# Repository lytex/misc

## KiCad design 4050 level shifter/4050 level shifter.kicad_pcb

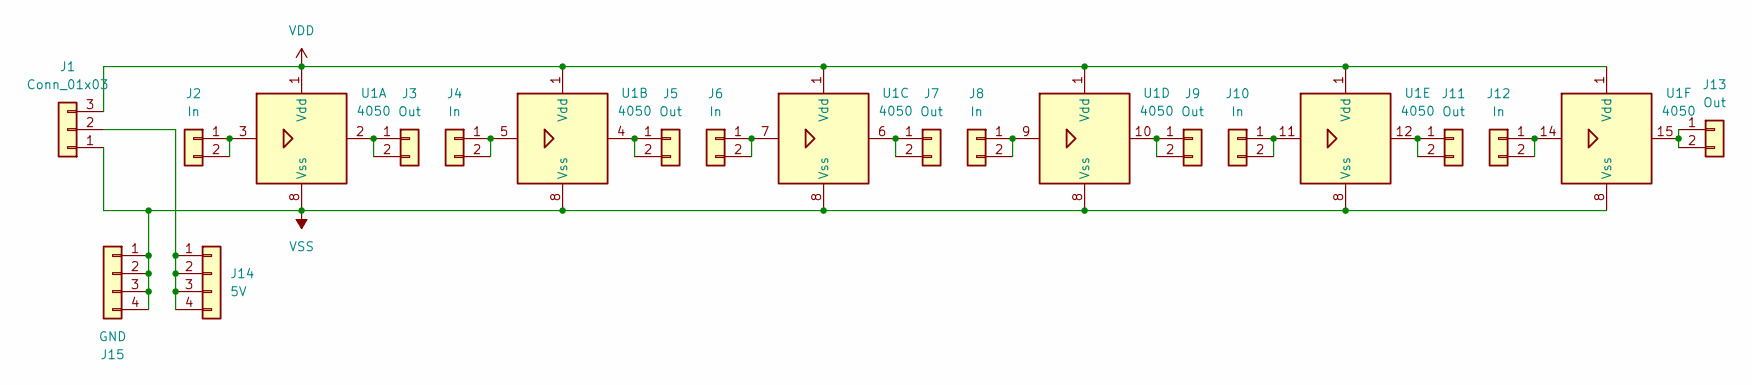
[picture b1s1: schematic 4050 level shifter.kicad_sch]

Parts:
J1: Conn_01x03; JST_EH_S3B-EH_1x03_P2.50mm_Horizontal
J2, J4, J6, J8, J10, J12: In; PinSocket_1x02_P2.54mm_Vertical
J3, J5, J7, J9, J11, J13: Out; PinSocket_1x02_P2.54mm_Vertical
J14: 5V; PinHeader_1x04_P2.54mm_Vertical
J15: GND; PinHeader_1x04_P2.54mm_Vertical
U1: 4050; DIP-16_W10.16mm

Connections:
unnamed: J1.2, J14.1, J14.2, J14.3, J14.4
unnamed: J2.1, J2.2, U1.3
unnamed: J3.1, J3.2, U1.2
unnamed: J4.1, J4.2, U1.5
unnamed: J5.1, J5.2, U1.4
unnamed: J6.1, J6.2, U1.7
unnamed: J7.1, J7.2, U1.6
unnamed: J8.1, J8.2, U1.9
unnamed: J9.1, J9.2, U1.10
unnamed: J10.1, J10.2, U1.11
unnamed: J11.1, J11.2, U1.12
unnamed: J12.1, J12.2, U1.14
unnamed: J13.1, J13.2, U1.15
VDD: J1.3, U1.1 (Vdd)
VSS: J1.1, J15.1, J15.2, J15.3, J15.4, U1.8 (Vss)

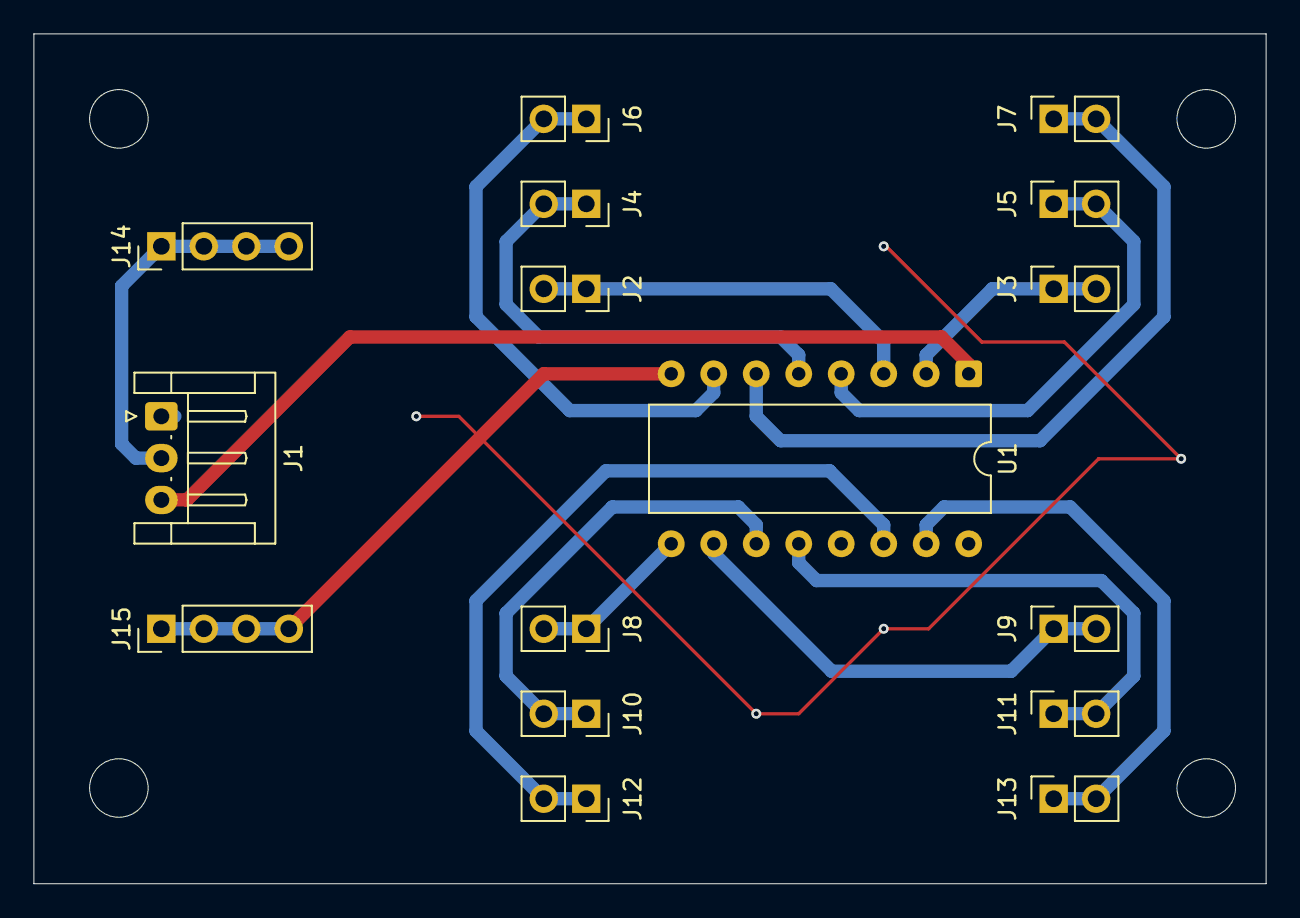
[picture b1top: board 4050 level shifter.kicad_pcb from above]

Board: 2 copper layers, 73.7 x 50.8 mm, 16 parts (0 on the bottom side), 15 nets.

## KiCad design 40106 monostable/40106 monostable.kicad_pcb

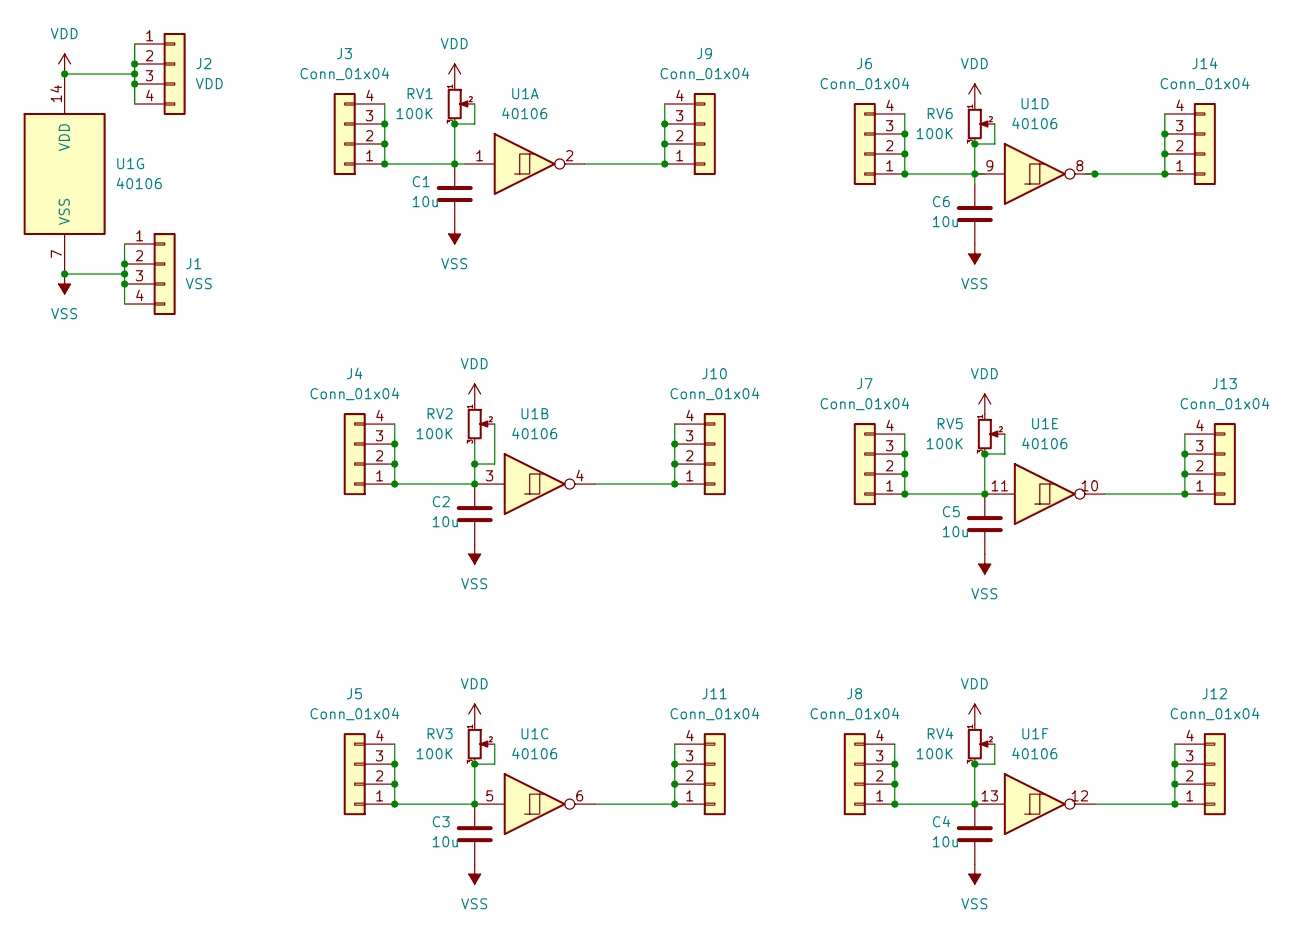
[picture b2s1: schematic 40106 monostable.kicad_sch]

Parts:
C1, C2, C3, C4, C5, C6: 10u; C_Disc_D7.5mm_W2.5mm_P5.00mm
J1: VSS; PinHeader_1x04_P2.54mm_Vertical
J2: VDD; PinHeader_1x04_P2.54mm_Vertical
J3, J4, J5, J6, J7, J8, J9, J10, J11, J12, J13, J14: Conn_01x04; PinHeader_1x04_P2.54mm_Vertical
RV1, RV2, RV3, RV4, RV5, RV6: 100K; Potentiometer_Alpha_RD901F-40-00D_Single_Vertical
U1: 40106; DIP-14_W10.16mm

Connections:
unnamed: C1.1, J3.1, J3.2, J3.3, J3.4, RV1.2, RV1.3, U1.1
unnamed: C2.1, J4.1, J4.2, J4.3, J4.4, RV2.2, RV2.3, U1.3
unnamed: C3.1, J5.1, J5.2, J5.3, J5.4, RV3.2, RV3.3, U1.5
unnamed: C6.1, J6.1, J6.2, J6.3, J6.4, RV6.2, RV6.3, U1.9
unnamed: C5.1, J7.1, J7.2, J7.3, J7.4, RV5.2, RV5.3, U1.11
unnamed: C4.1, J8.1, J8.2, J8.3, J8.4, RV4.2, RV4.3, U1.13
unnamed: J9.1, J9.2, J9.3, J9.4, U1.2
unnamed: J10.1, J10.2, J10.3, J10.4, U1.4
unnamed: J11.1, J11.2, J11.3, J11.4, U1.6
unnamed: J12.1, J12.2, J12.3, J12.4, U1.12
unnamed: J13.1, J13.2, J13.3, J13.4, U1.10
unnamed: J14.1, J14.2, J14.3, J14.4, U1.8
VDD: J2.1, J2.2, J2.3, J2.4, RV1.1, RV2.1, RV3.1, RV4.1, RV5.1, RV6.1, U1.14 (VDD)
VSS: C1.2, C2.2, C3.2, C4.2, C5.2, C6.2, J1.1, J1.2, J1.3, J1.4, U1.7 (VSS)

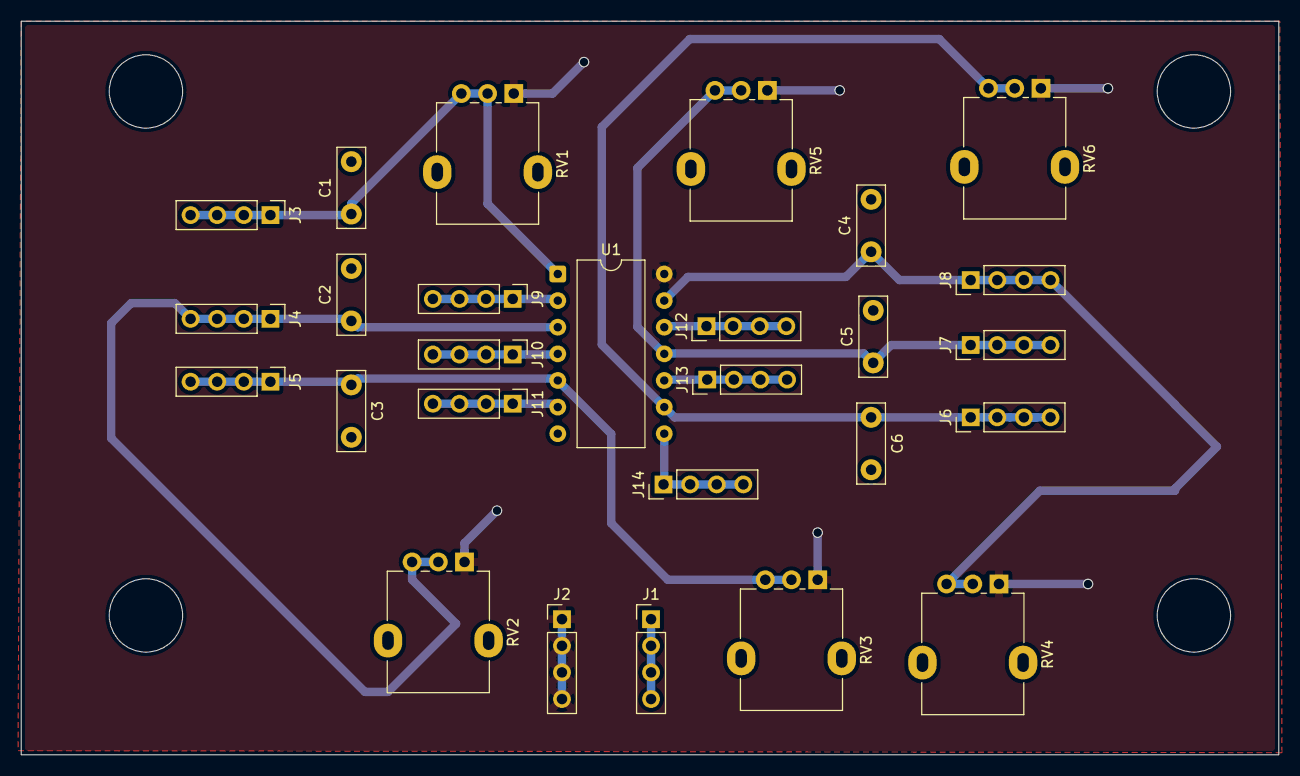
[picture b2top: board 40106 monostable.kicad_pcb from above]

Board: 2 copper layers, 120.0 x 70.0 mm, 27 parts (0 on the bottom side), 14 nets.

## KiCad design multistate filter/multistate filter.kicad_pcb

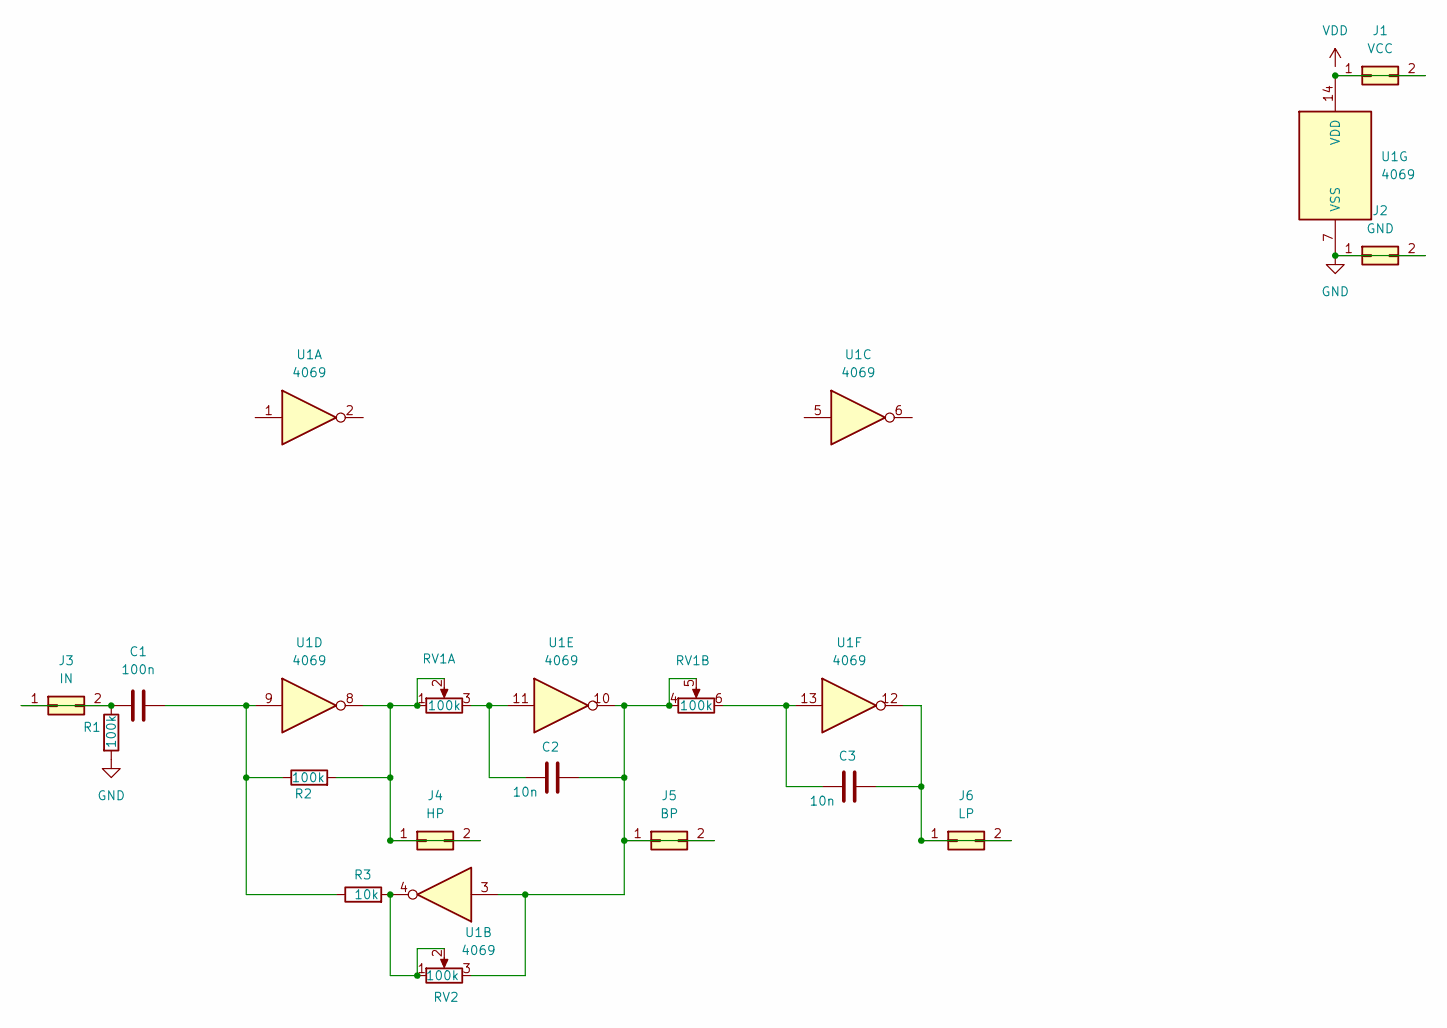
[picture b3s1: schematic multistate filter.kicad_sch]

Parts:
C1: 100n; C_Disc_D3.0mm_W1.6mm_P2.50mm
C2, C3: 10n; C_Disc_D3.0mm_W1.6mm_P2.50mm
J1: VCC; PinHeader_2x01_P2.54mm_Vertical
J2: GND; PinHeader_2x01_P2.54mm_Vertical
J3: IN; PinHeader_2x01_P2.54mm_Vertical
J4: HP; PinHeader_2x01_P2.54mm_Vertical
J5: BP; PinHeader_2x01_P2.54mm_Vertical
J6: LP; PinHeader_2x01_P2.54mm_Vertical
R1, R2: 100k; R_Axial_DIN0207_L6.3mm_D2.5mm_P10.16mm_Horizontal
R3: 10k; R_Axial_DIN0207_L6.3mm_D2.5mm_P10.16mm_Horizontal
RV1: 100k; Potentiometer_Alps_RK163_Dual_Horizontal
RV2: 100k; Potentiometer_Alps_RK163_Single_Horizontal
U1: 4069; DIP-14_W7.62mm

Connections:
GND: J2.1, J2.2, R1.2, U1.7 (VSS)
unnamed: C1.2, R2.1, R3.1, U1.9
unnamed: C2.1, RV1.3, U1.11
unnamed: C3.1, RV1.6, U1.13
unnamed: J1.1, J1.2, U1.14 (VDD)
unnamed: C1.1, J3.1, J3.2, R1.1
unnamed: J4.1, J4.2, R2.2, RV1.1, RV1.2, U1.8
unnamed: C2.2, J5.1, J5.2, RV1.4, RV1.5, RV2.3, U1.3, U1.10
unnamed: C3.2, J6.1, J6.2, U1.12
unnamed: R3.2, RV2.1, RV2.2, U1.4

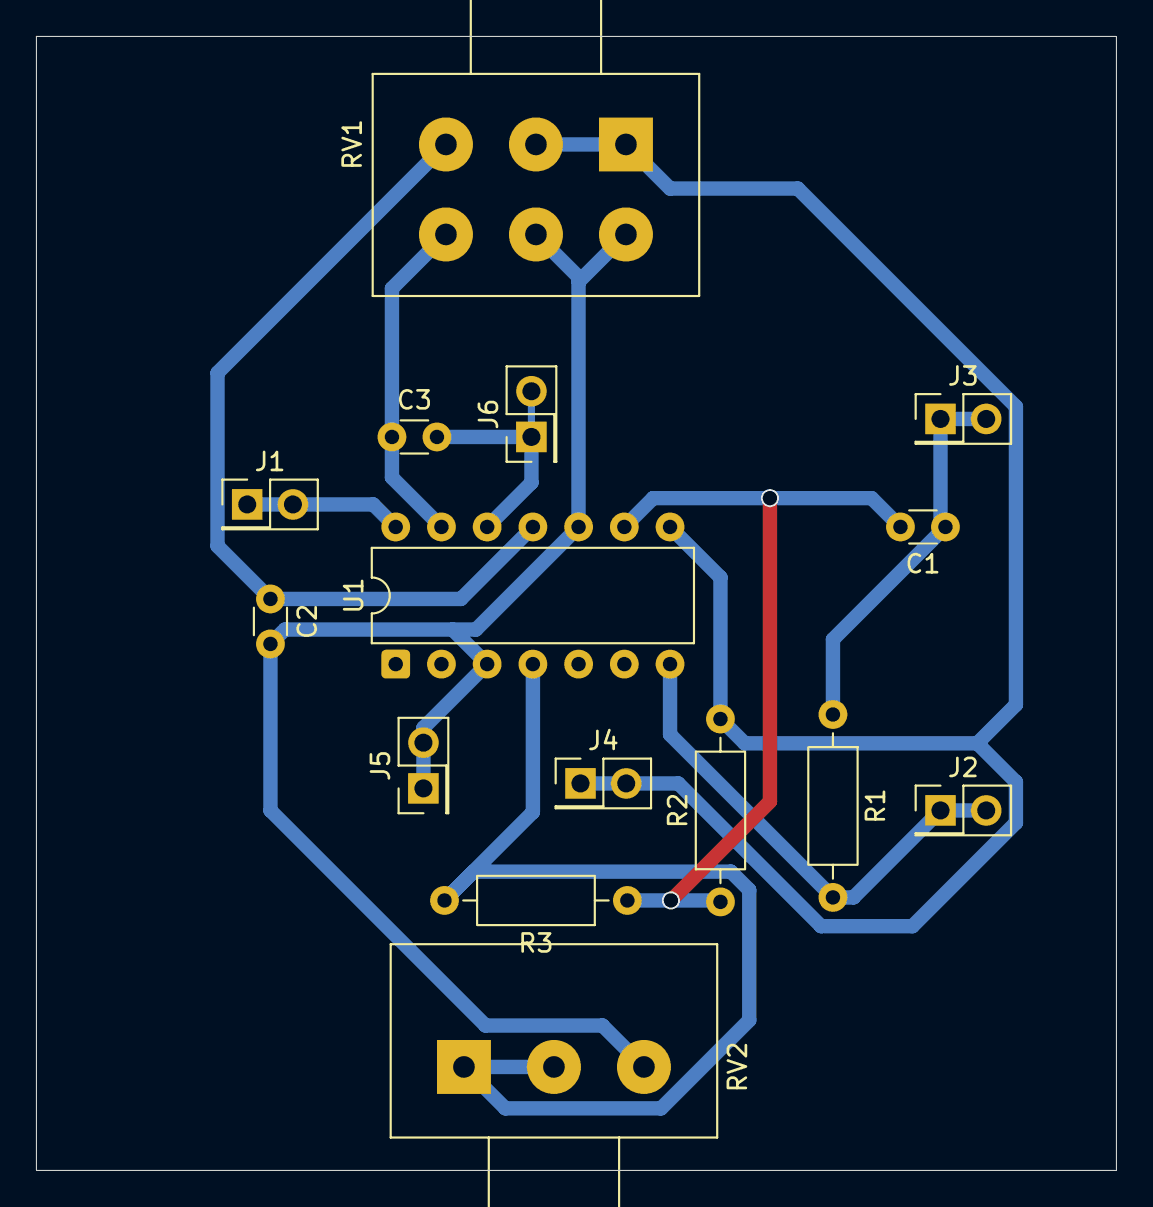
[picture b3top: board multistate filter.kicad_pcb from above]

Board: 2 copper layers, 60.0 x 63.0 mm, 15 parts (0 on the bottom side), 10 nets.

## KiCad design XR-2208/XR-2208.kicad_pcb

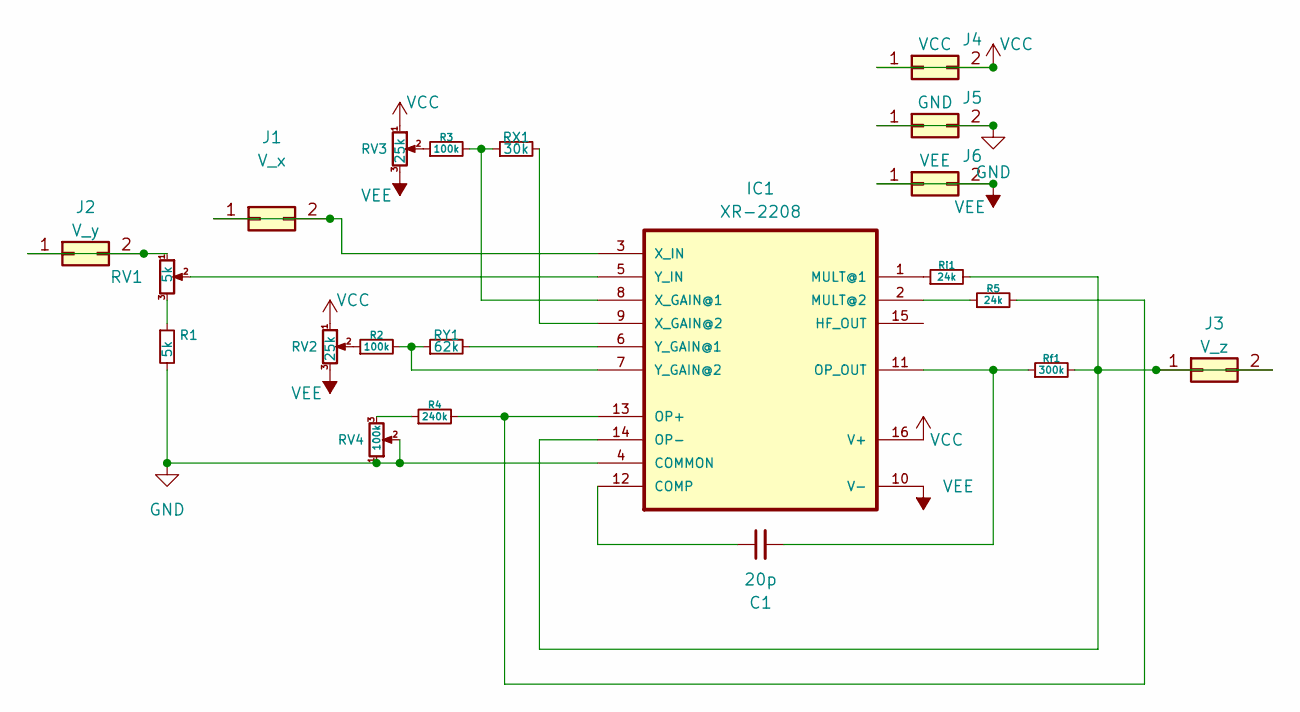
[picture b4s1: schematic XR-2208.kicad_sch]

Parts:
C1: 20p; C_Disc_D3.0mm_W1.6mm_P2.50mm
IC1: XR-2208; DIP-16_W7.62mm
J1: V_x; PinHeader_2x01_P2.54mm_Vertical
J2: V_y; PinHeader_2x01_P2.54mm_Vertical
J3: V_z; PinHeader_2x01_P2.54mm_Vertical
J4: VCC; PinHeader_2x01_P2.54mm_Vertical
J5: GND; PinHeader_2x01_P2.54mm_Vertical
J6: VEE; PinHeader_2x01_P2.54mm_Vertical
R1: 5k; R_Axial_DIN0207_L6.3mm_D2.5mm_P10.16mm_Horizontal
R2, R3: 100k; R_Axial_DIN0207_L6.3mm_D2.5mm_P10.16mm_Horizontal
R4: 240k; R_Axial_DIN0207_L6.3mm_D2.5mm_P10.16mm_Horizontal
R5: 24k; R_Axial_DIN0207_L6.3mm_D2.5mm_P10.16mm_Horizontal
RV1: 5k; Potentiometer_Bourns_3296W_Vertical
RV2, RV3: 25k; Potentiometer_Bourns_3296W_Vertical
RV4: 100k; Potentiometer_Bourns_3296W_Vertical
RX1: 30k; R_Axial_DIN0207_L6.3mm_D2.5mm_P10.16mm_Horizontal
RY1: 62k; R_Axial_DIN0207_L6.3mm_D2.5mm_P10.16mm_Horizontal
Rf1: 300k; R_Axial_DIN0207_L6.3mm_D2.5mm_P10.16mm_Horizontal
Ri1: 24k; R_Axial_DIN0207_L6.3mm_D2.5mm_P10.16mm_Horizontal

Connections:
GND: IC1.4 (COMMON), J5.1, J5.2, R1.2, RV4.1, RV4.2
unnamed: C1.1, IC1.12 (COMP)
unnamed: IC1.1 (MULT@1), Ri1.1
unnamed: IC1.2 (MULT@2), R5.1
unnamed: IC1.13 (OP+), R4.2, R5.2
unnamed: IC1.14 (OP-), J3.1, J3.2, Rf1.2, Ri1.2
unnamed: C1.2, IC1.11 (OP_OUT), Rf1.1
unnamed: IC1.8 (X_GAIN@1), R3.2, RX1.1
unnamed: IC1.9 (X_GAIN@2), RX1.2
unnamed: IC1.3 (X_IN), J1.1, J1.2
unnamed: IC1.6 (Y_GAIN@1), RY1.2
unnamed: IC1.7 (Y_GAIN@2), R2.2, RY1.1
unnamed: IC1.5 (Y_IN), RV1.2
unnamed: J2.1, J2.2, RV1.1
unnamed: R1.1, RV1.3
unnamed: R2.1, RV2.2
unnamed: R3.1, RV3.2
unnamed: R4.1, RV4.3
VCC: IC1.16 (V+), J4.1, J4.2, RV2.1, RV3.1
VEE: IC1.10 (V-), J6.1, J6.2, RV2.3, RV3.3

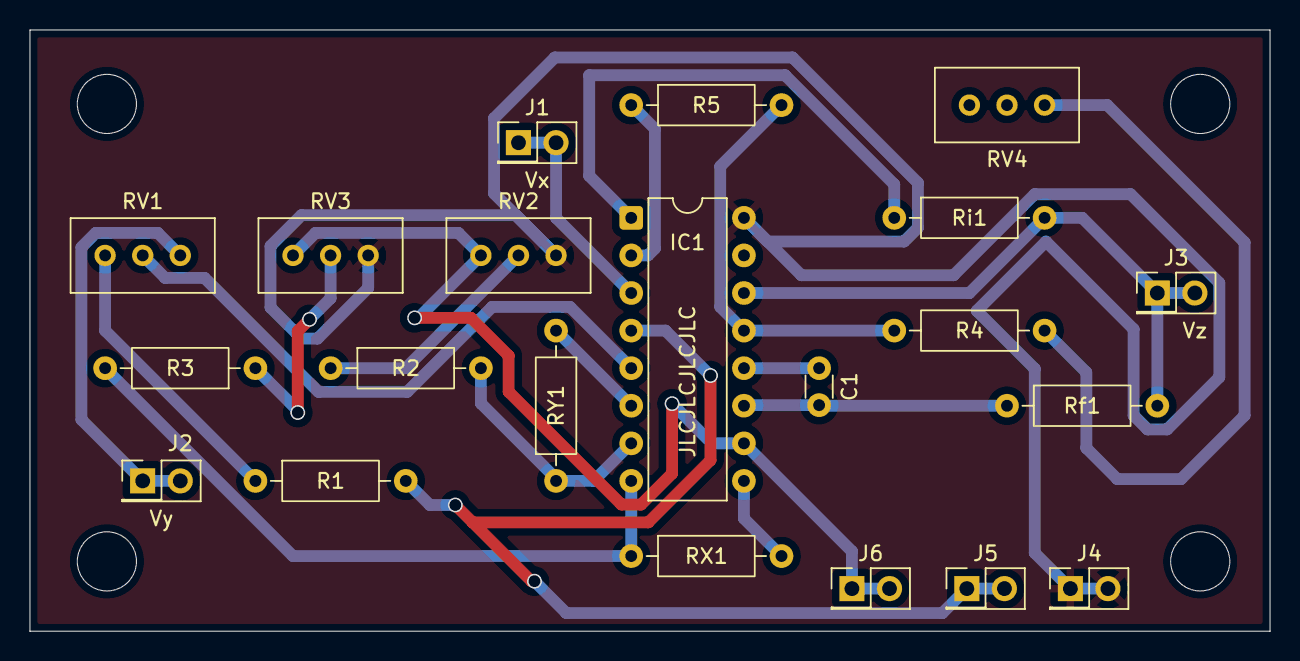
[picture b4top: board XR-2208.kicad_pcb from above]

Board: 2 copper layers, 83.8 x 40.6 mm, 21 parts (0 on the bottom side), 20 nets.

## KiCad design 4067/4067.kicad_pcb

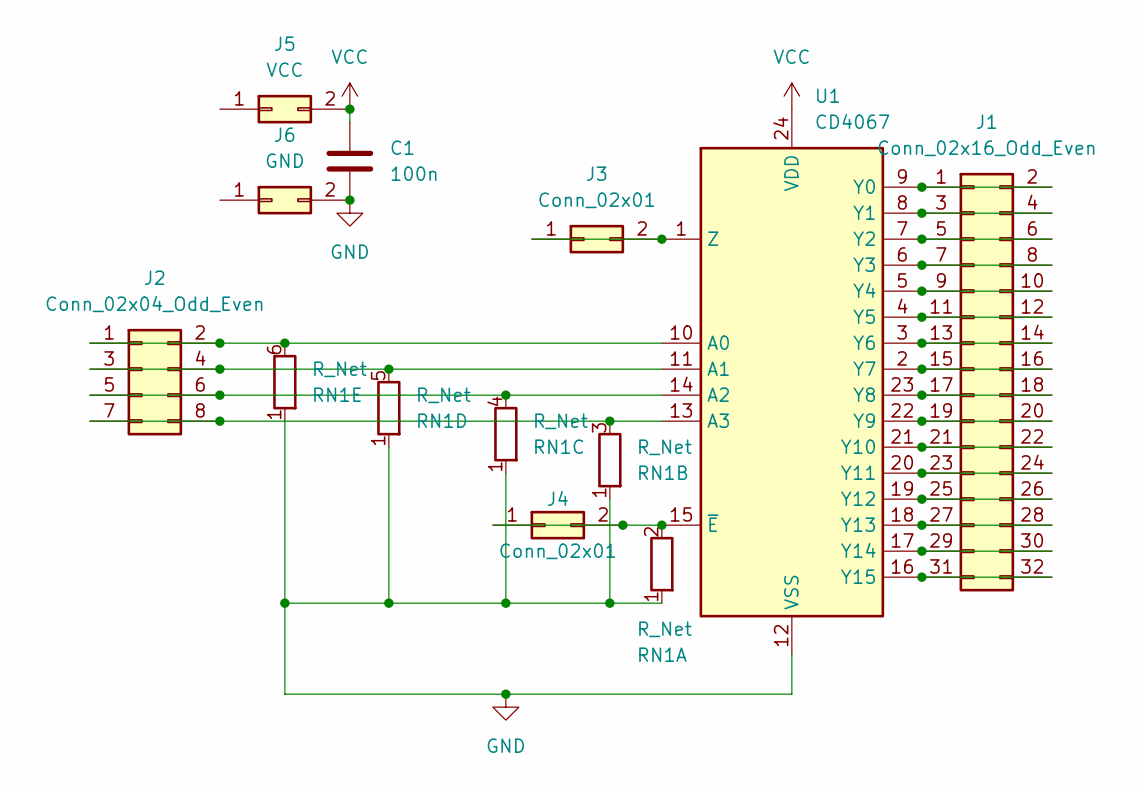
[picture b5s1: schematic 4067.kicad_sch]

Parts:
C1: 100n; C_Disc_D5.0mm_W2.5mm_P2.50mm
J1: Conn_02x16_Odd_Even; PinHeader_2x16_P2.54mm_Vertical
J2: Conn_02x04_Odd_Even; PinHeader_2x04_P2.54mm_Vertical
J3, J4: Conn_02x01; PinHeader_2x01_P2.54mm_Vertical
J5: VCC; PinHeader_2x01_P2.54mm_Vertical
J6: GND; PinHeader_2x01_P2.54mm_Vertical
RN1: R_Net; R_Array_SIP6
U1: CD4067; DIP-24_18.0mmx34.29mm_W15.24mm

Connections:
GND: C1.2, J6.2, RN1.1 (R1), U1.12 (VSS)
unnamed: J1.1, J1.2, U1.9 (Y0)
unnamed: J1.3, J1.4, U1.8 (Y1)
unnamed: J1.5, J1.6, U1.7 (Y2)
unnamed: J1.7, J1.8, U1.6 (Y3)
unnamed: J1.9, J1.10, U1.5 (Y4)
unnamed: J1.11, J1.12, U1.4 (Y5)
unnamed: J1.13, J1.14, U1.3 (Y6)
unnamed: J1.15, J1.16, U1.2 (Y7)
unnamed: J1.17, J1.18, U1.23 (Y8)
unnamed: J1.19, J1.20, U1.22 (Y9)
unnamed: J1.21, J1.22, U1.21 (Y10)
unnamed: J1.23, J1.24, U1.20 (Y11)
unnamed: J1.25, J1.26, U1.19 (Y12)
unnamed: J1.27, J1.28, U1.18 (Y13)
unnamed: J1.29, J1.30, U1.17 (Y14)
unnamed: J1.31, J1.32, U1.16 (Y15)
unnamed: J2.1, J2.2, RN1.6 (R5.2), U1.10 (A0)
unnamed: J2.3, J2.4, RN1.5 (R4.2), U1.11 (A1)
unnamed: J2.5, J2.6, RN1.4 (R3.2), U1.14 (A2)
unnamed: J2.7, J2.8, RN1.3 (R2.2), U1.13 (A3)
unnamed: J3.1, J3.2, U1.1 (Z)
unnamed: J4.1, J4.2, RN1.2 (R1.2), U1.15 (~E)
VCC: C1.1, J5.2, U1.24 (VDD)

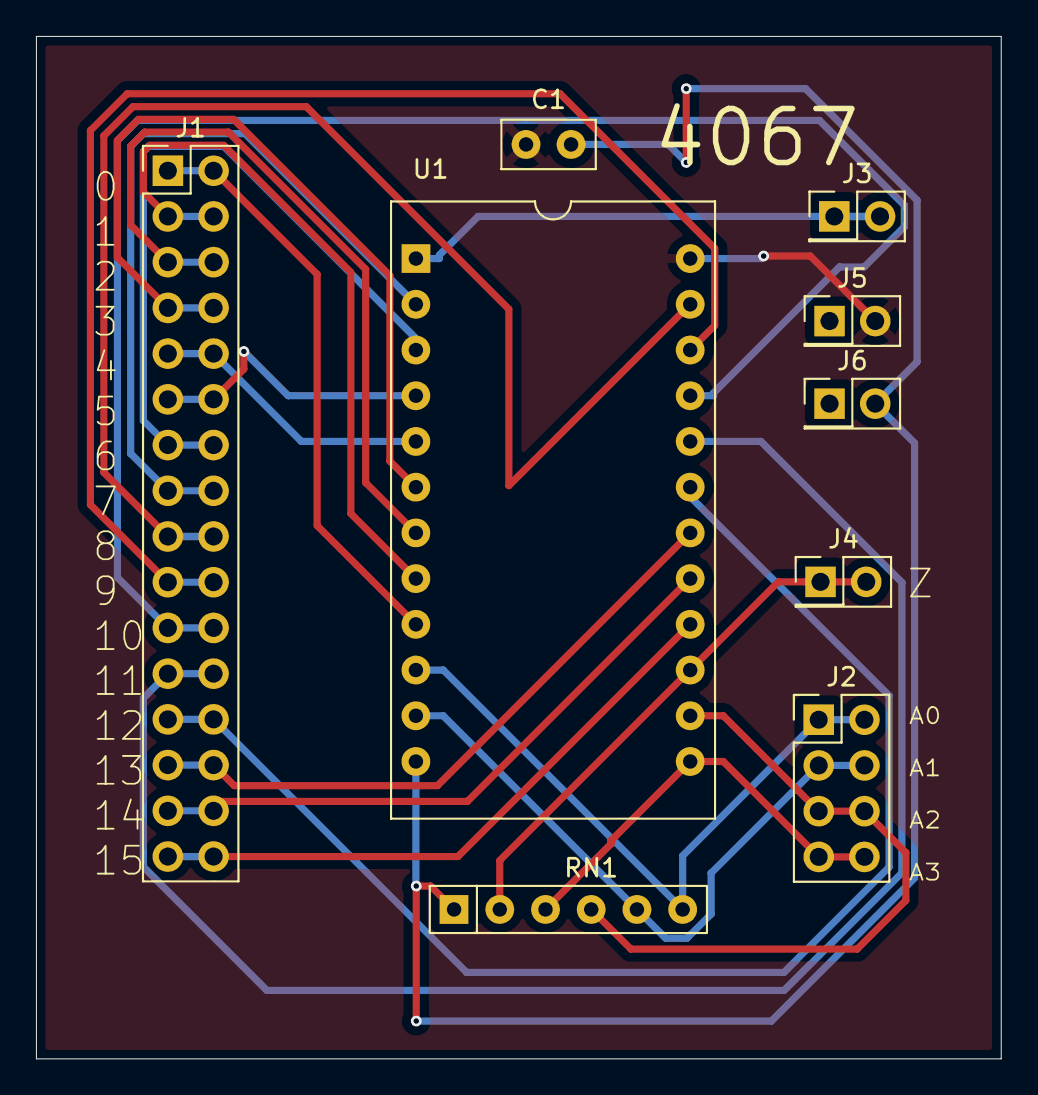
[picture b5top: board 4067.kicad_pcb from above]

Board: 2 copper layers, 53.6 x 56.8 mm, 9 parts (0 on the bottom side), 24 nets.

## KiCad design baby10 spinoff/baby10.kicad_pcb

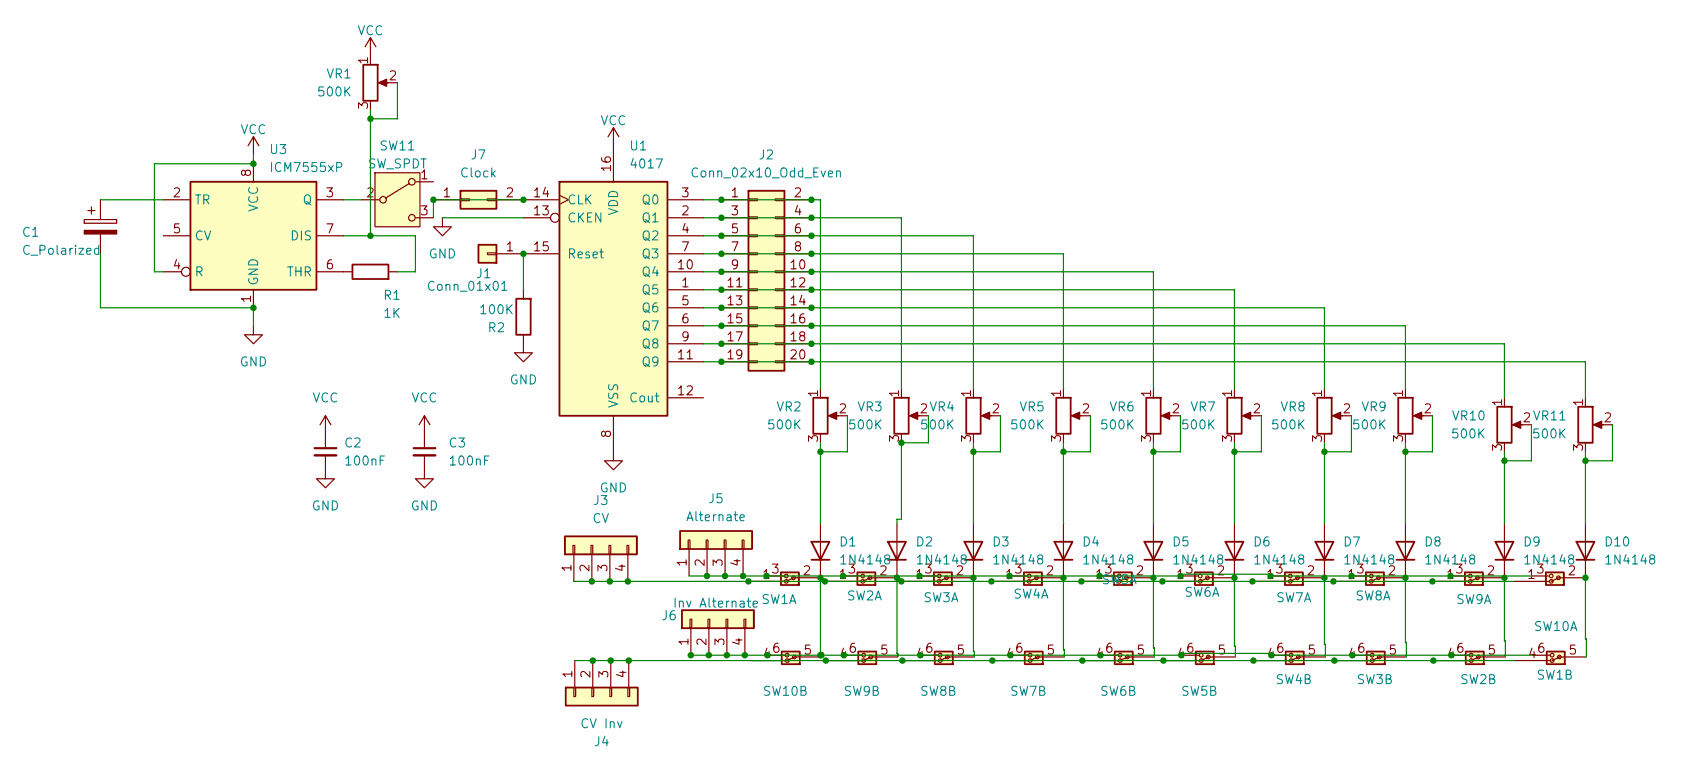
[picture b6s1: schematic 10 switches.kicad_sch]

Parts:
C1: C_Polarized; CP_Radial_D5.0mm_P2.50mm
C2, C3: 100nF; C_Disc_D3.0mm_W1.6mm_P2.50mm
D1, D2, D3, D4, D5, D6, D7, D8, D9, D10: 1N4148; D_DO-35_SOD27_P7.62mm_Horizontal
J1: Conn_01x01; PinHeader_1x01_P2.54mm_Vertical
J2: Conn_02x10_Odd_Even; PinHeader_2x10_P2.54mm_Vertical
J3: CV; PinHeader_1x04_P2.54mm_Vertical
J4: CV Inv; PinHeader_1x04_P2.54mm_Vertical
J5: Alternate; PinHeader_1x04_P2.54mm_Vertical
J6: Inv Alternate; PinHeader_1x04_P2.54mm_Vertical
J7: Clock; PinHeader_2x01_P2.54mm_Vertical
R1: 1K; R_Axial_DIN0207_L6.3mm_D2.5mm_P10.16mm_Horizontal
R2: 100K; R_Axial_DIN0207_L6.3mm_D2.5mm_P10.16mm_Horizontal
SW1, SW2, SW3, SW4, SW5, SW6, SW7, SW8, SW9, SW10: SW_DPDT_x2_Latching; SW_DPDT_x2_Latching_2mm_pitch
SW11: SW_SPDT; SW_CK_JS202011CQN_DPDT_Straight
U1: 4017; DIP-16_W7.62mm
U3: ICM7555xP; DIP-8_W7.62mm
VR1, VR2, VR3, VR4, VR5, VR6, VR7, VR8, VR9, VR10, VR11: 500K; Potentiometer_Alps_RK097_Single_Horizontal

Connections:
GND: C1.2, C2.2, C3.2, R2.1, U1.8 (VSS), U1.13 (CKEN), U3.1 (GND)
unnamed: D1.2 (A), VR2.2, VR2.3
unnamed: D1.1 (K), J6.1, J6.2, J6.3, J6.4, SW1.2 (B), SW1.6 (C), SW2.6 (C), SW3.6 (C), SW4.6 (C), SW5.6 (C), SW6.6 (C), SW7.6 (C), SW8.6 (C), SW9.6 (C), SW10.5 (B), SW10.6 (C)
unnamed: D2.2 (A), VR3.2, VR3.3
unnamed: D2.1 (K), SW2.2 (B), SW9.5 (B)
unnamed: D3.2 (A), VR4.2, VR4.3
unnamed: D3.1 (K), SW3.2 (B), SW8.5 (B)
unnamed: D4.2 (A), VR5.2, VR5.3
unnamed: D4.1 (K), SW4.2 (B), SW7.5 (B)
unnamed: D5.2 (A), VR6.2, VR6.3
unnamed: D5.1 (K), SW5.2 (B), SW6.5 (B)
unnamed: D6.2 (A), VR7.2, VR7.3
unnamed: D6.1 (K), SW5.5 (B), SW6.2 (B)
unnamed: D7.2 (A), VR8.2, VR8.3
unnamed: D7.1 (K), SW4.5 (B), SW7.2 (B)
unnamed: D8.2 (A), VR9.2, VR9.3
unnamed: D8.1 (K), SW3.5 (B), SW8.2 (B)
unnamed: D9.2 (A), VR10.2, VR10.3
unnamed: D9.1 (K), SW2.5 (B), SW9.2 (B)
unnamed: D10.2 (A), VR11.2, VR11.3
unnamed: D10.1 (K), SW1.5 (B), SW10.2 (B)
unnamed: J1.1, R2.2, U1.15 (Reset)
unnamed: J2.1, J2.2, U1.3 (Q0), VR2.1
unnamed: J2.3, J2.4, U1.2 (Q1), VR3.1
unnamed: J2.5, J2.6, U1.4 (Q2), VR4.1
unnamed: J2.7, J2.8, U1.7 (Q3), VR5.1
unnamed: J2.9, J2.10, U1.10 (Q4), VR6.1
unnamed: J2.11, J2.12, U1.1 (Q5), VR7.1
unnamed: J2.13, J2.14, U1.5 (Q6), VR8.1
unnamed: J2.15, J2.16, U1.6 (Q7), VR9.1
unnamed: J2.17, J2.18, U1.9 (Q8), VR10.1
unnamed: J2.19, J2.20, U1.11 (Q9), VR11.1
unnamed: J3.1, J3.2, J3.3, J3.4, SW1.1 (A), SW2.1 (A), SW3.1 (A), SW4.1 (A), SW5.1 (A), SW6.1 (A), SW7.1 (A), SW8.1 (A), SW9.1 (A), SW10.1 (A)
unnamed: J4.1, J4.2, J4.3, J4.4, SW10.4 (A)
unnamed: J5.1, J5.2, J5.3, J5.4, SW1.3 (C), SW2.3 (C), SW3.3 (C), SW4.3 (C), SW5.3 (C), SW6.3 (C), SW7.3 (C), SW8.3 (C), SW9.3 (C), SW10.3 (C)
unnamed: J7.1, J7.2, SW11.3 (C), U1.14 (CLK)
unnamed: SW1.4 (A), SW2.4 (A), SW3.4 (A), SW4.4 (A), SW5.4 (A), SW6.4 (A), SW7.4 (A), SW8.4 (A), SW9.4 (A)
unnamed: SW11.2 (B), U3.3 (Q)
unnamed: R1.2, U3.7 (DIS), VR1.2, VR1.3
unnamed: R1.1, U3.6 (THR)
unnamed: C1.1, U3.2 (TR)
VCC: C2.1, C3.1, U1.16 (VDD), U3.4 (R), U3.8 (VCC), VR1.1

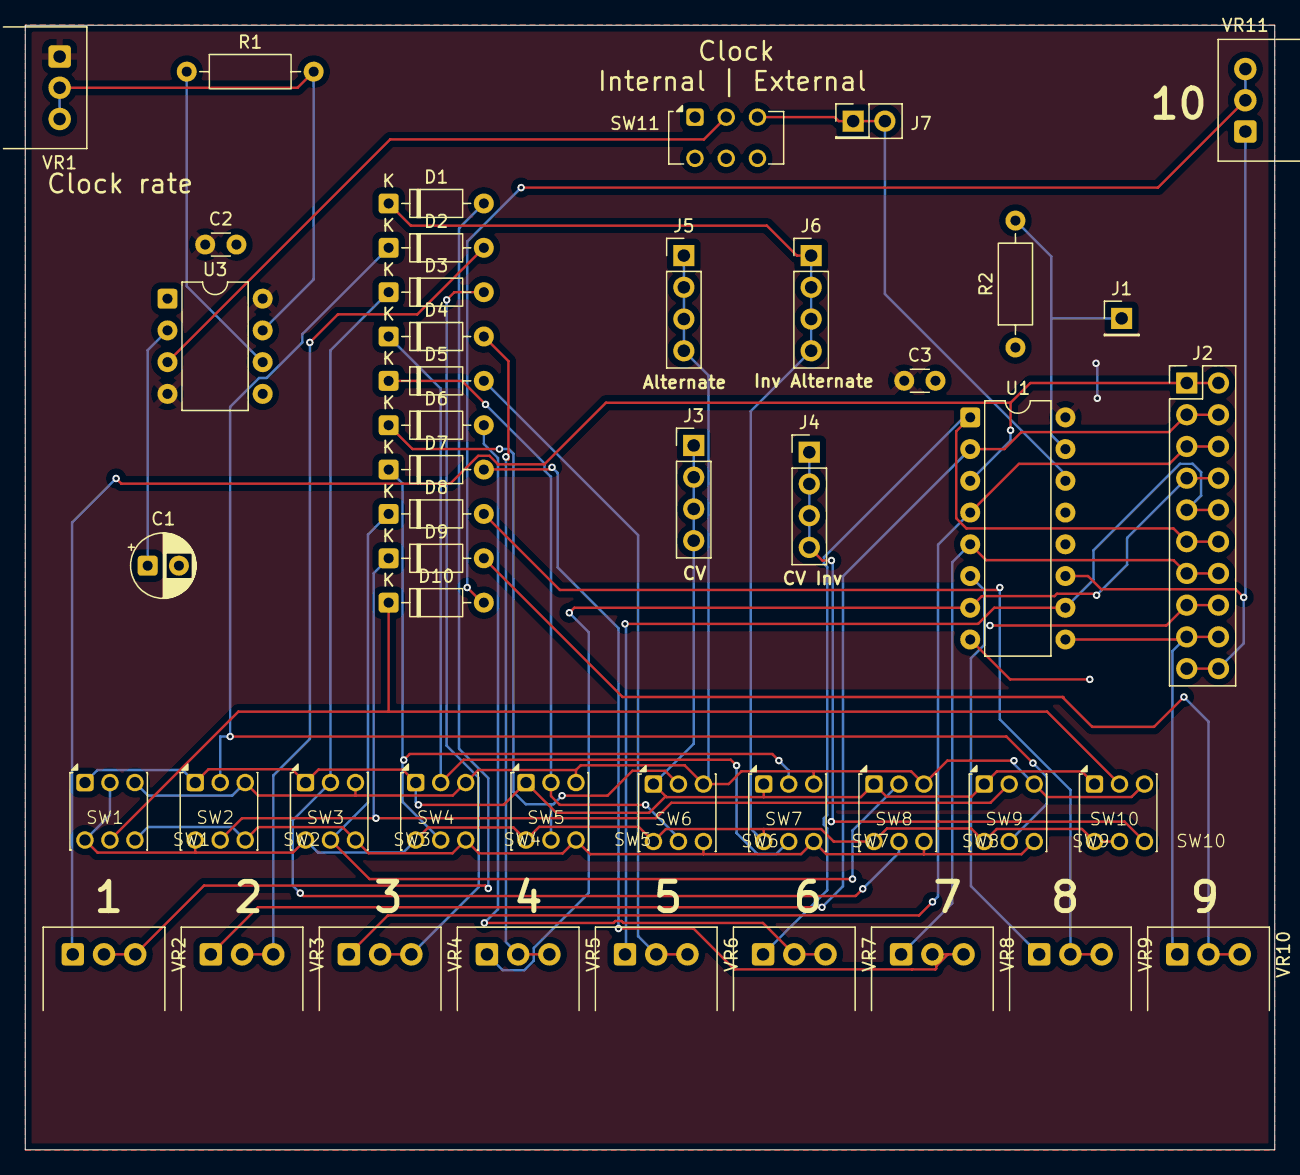
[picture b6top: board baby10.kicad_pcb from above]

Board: 2 copper layers, 100.0 x 90.0 mm, 46 parts (0 on the bottom side), 42 nets.

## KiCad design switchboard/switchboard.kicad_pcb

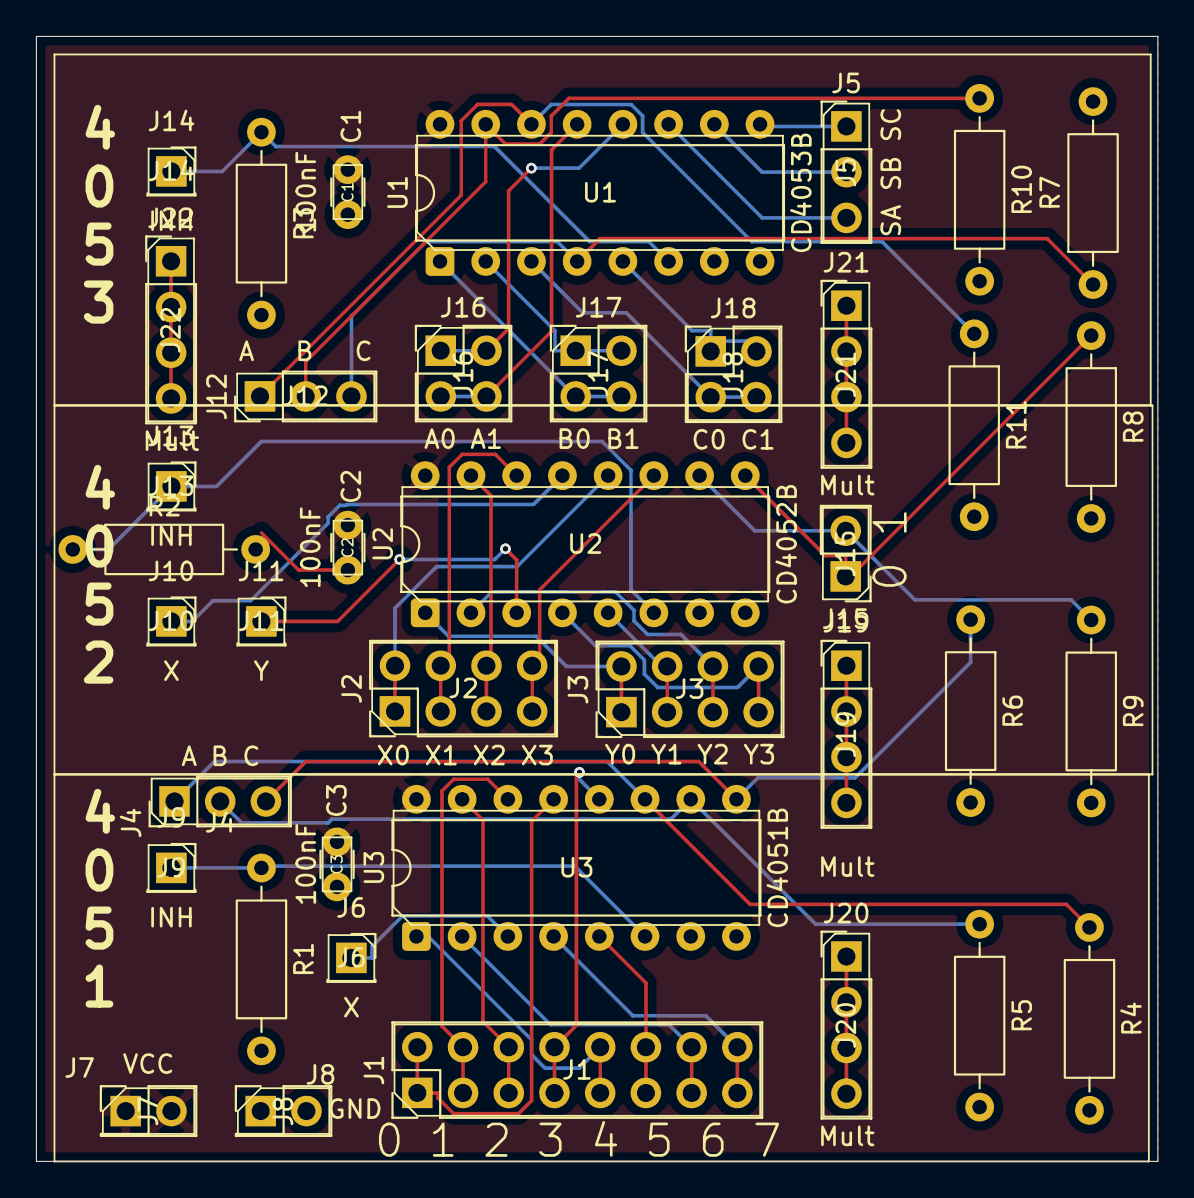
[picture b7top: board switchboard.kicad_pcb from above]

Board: 2 copper layers, 62.3 x 62.5 mm, 39 parts (0 on the bottom side), 45 nets.

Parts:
C1, C2, C3: 100nF; C_Disc_D3.0mm_W1.6mm_P2.50mm
J1: 0 1 2 3 4 5 6 7; PinHeader_2x08_P2.54mm_Vertical
J2: X0 X1 X2 X3; PinHeader_2x04_P2.54mm_Vertical
J3: Y0 Y1 Y2 Y3; PinHeader_2x04_P2.54mm_Vertical
J4, J12: A B C; PinHeader_1x03_P2.54mm_Vertical
J5: SA SB SC; PinHeader_1x03_P2.54mm_Vertical
J6, J10: X; PinSocket_1x01_P2.54mm_Vertical
J7: VCC; PinHeader_2x01_P2.54mm_Vertical
J8: GND; PinHeader_2x01_P2.54mm_Vertical
J9, J13, J14: INH; PinSocket_1x01_P2.54mm_Vertical
J11: Y; PinSocket_1x01_P2.54mm_Vertical
J15: 0 1; PinHeader_1x02_P2.54mm_Vertical
J16: A0 A1; PinHeader_2x02_P2.54mm_Vertical
J17: B0 B1; PinHeader_2x02_P2.54mm_Vertical
J18: C0 C1; PinHeader_2x02_P2.54mm_Vertical
J19, J20, J21, J22: Mult; PinHeader_1x04_P2.54mm_Vertical
R1, R2, R3, R4, R5, R6, R7, R8, R9, R10, R11: 100k; R_Axial_DIN0207_L6.3mm_D2.5mm_P10.16mm_Horizontal
U1: CD4053B; DIP-16_W7.62mm
U2: CD4052B; DIP-16_W7.62mm
U3: CD4051B; DIP-16_W7.62mm

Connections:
GND: C1.2, C2.2, C3.2, J8.2, R1.2, R2.2, R3.2, R4.2, R5.2, R6.2, R7.2, R8.2, R9.2, R10.2, R11.2, U1.7 (VEE), U1.8 (VSS), U2.7 (VEE), U2.8 (VSS), U3.7 (VEE), U3.8 (VSS)
unnamed: J1.1, J1.2, U3.13 (X0)
unnamed: J1.3, J1.4, U3.14 (X1)
unnamed: J1.5, J1.6, U3.15 (X2)
unnamed: J1.7, J1.8, U3.12 (X3)
unnamed: J1.9, J1.10, U3.1 (X4)
unnamed: J1.11, J1.12, U3.5 (X5)
unnamed: J1.13, J1.14, U3.2 (X6)
unnamed: J1.15, J1.16, U3.4 (X7)
unnamed: J2.1, J2.2, U2.12 (X0)
unnamed: J2.3, J2.4, U2.14 (X1)
unnamed: J2.5, J2.6, U2.15 (X2)
unnamed: J2.7, J2.8, U2.11 (X3)
unnamed: J3.1, J3.2, U2.1 (Y0)
unnamed: J3.3, J3.4, U2.5 (Y1)
unnamed: J3.5, J3.6, U2.2 (Y2)
unnamed: J3.7, J3.8, U2.4 (Y3)
unnamed: J4.1, R4.1, U3.11 (A)
unnamed: J4.2, R5.1, U3.10 (B)
unnamed: J4.3, R6.1, U3.9 (C)
unnamed: J5.1, U1.9 (S3)
unnamed: J5.2, U1.10 (S2)
unnamed: J5.3, U1.11 (S1)
unnamed: J6.1, U3.3 (X)
unnamed: J9.1, R1.1, U3.6 (INH)
unnamed: J10.1, U2.13 (X)
unnamed: J11.1, U2.3 (Y)
unnamed: J12.1, R11.1, U1.14 (A)
unnamed: J12.2, R10.1, U1.15 (B)
unnamed: J12.3, R7.1, U1.4 (C)
unnamed: J13.1, R2.1, U2.6 (INH)
unnamed: J14.1, R3.1, U1.6 (INH)
unnamed: J15.1, R8.1, U2.9 (B)
unnamed: J15.2, R9.1, U2.10 (A)
unnamed: J16.1, J16.2, U1.12 (A0)
unnamed: J16.3, J16.4, U1.13 (A1)
unnamed: J17.1, J17.2, U1.2 (B0)
unnamed: J17.3, J17.4, U1.1 (B1)
unnamed: J18.1, J18.2, U1.5 (C0)
unnamed: J18.3, J18.4, U1.3 (C1)
unnamed: J19.1, J19.2, J19.3, J19.4
unnamed: J20.1, J20.2, J20.3, J20.4
unnamed: J21.1, J21.2, J21.3, J21.4
unnamed: J22.1, J22.2, J22.3, J22.4
VCC: C1.1, C2.1, C3.1, J7.1, J7.2, U1.16 (VDD), U2.16 (VDD), U3.16 (VDD)
